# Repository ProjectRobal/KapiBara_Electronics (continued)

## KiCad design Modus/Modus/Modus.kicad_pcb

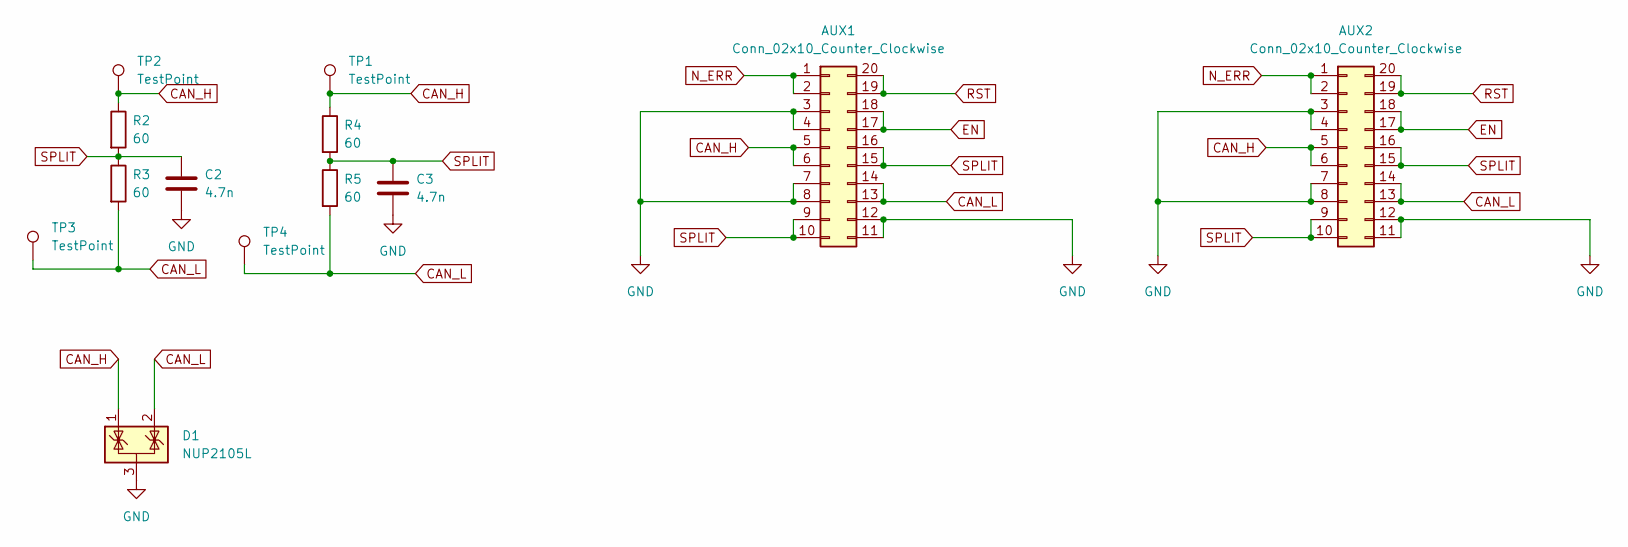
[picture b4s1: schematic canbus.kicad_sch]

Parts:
AUX1, AUX2: Conn_02x10_Counter_Clockwise; IDC-Header_2x10_P2.54mm_Vertical
C2, C3: 4.7n; C_0805_2012Metric_Pad1.18x1.45mm_HandSolder
D1: NUP2105L; SOT-23
R2, R3, R4, R5: 60; R_0805_2012Metric_Pad1.20x1.40mm_HandSolder
TP1, TP2, TP3, TP4: TestPoint; TestPoint_Pad_D2.0mm

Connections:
CAN_H: AUX1.5, AUX1.6, AUX2.5, AUX2.6, D1.1 (K), R2.1, R4.1, TP1.1, TP2.1; also elsewhere on the board
CAN_L: AUX1.13, AUX1.14, AUX2.13, AUX2.14, D1.2 (K), R3.2, R5.2, TP3.1, TP4.1; also elsewhere on the board
EN: AUX1.17, AUX1.18, AUX2.17, AUX2.18; also elsewhere on the board
GND: AUX1.3, AUX1.4, AUX1.7, AUX1.8, AUX1.11, AUX1.12, AUX2.3, AUX2.4, AUX2.7, AUX2.8, AUX2.11, AUX2.12, C2.2, C3.2, D1.3 (A); also elsewhere on the board
N_ERR: AUX1.1, AUX1.2, AUX2.1, AUX2.2; also elsewhere on the board
RST: AUX1.19, AUX1.20, AUX2.19, AUX2.20; also elsewhere on the board
SPLIT: AUX1.9, AUX1.10, AUX1.15, AUX1.16, AUX2.9, AUX2.10, AUX2.15, AUX2.16, C2.1, C3.1, R2.2, R3.1, R4.2, R5.1; also elsewhere on the board

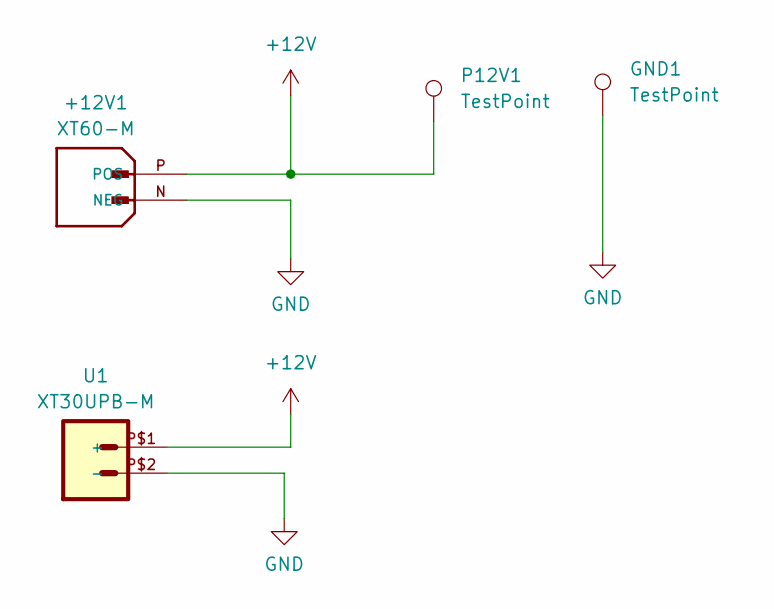
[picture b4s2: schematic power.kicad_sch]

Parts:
+12V1: XT60-M; AMASS_XT60-M; PARTREV V1.2
GND1: TestPoint; TestPoint_Pad_3.0x3.0mm
P12V1: TestPoint; TestPoint_Pad_3.0x3.0mm
U1: XT30UPB-M

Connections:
+12V: +12V1.P (POS), P12V1.1, U1.P$1 (+); also elsewhere on the board
GND: +12V1.N (NEG), GND1.1, U1.P$2 (-); also elsewhere on the board

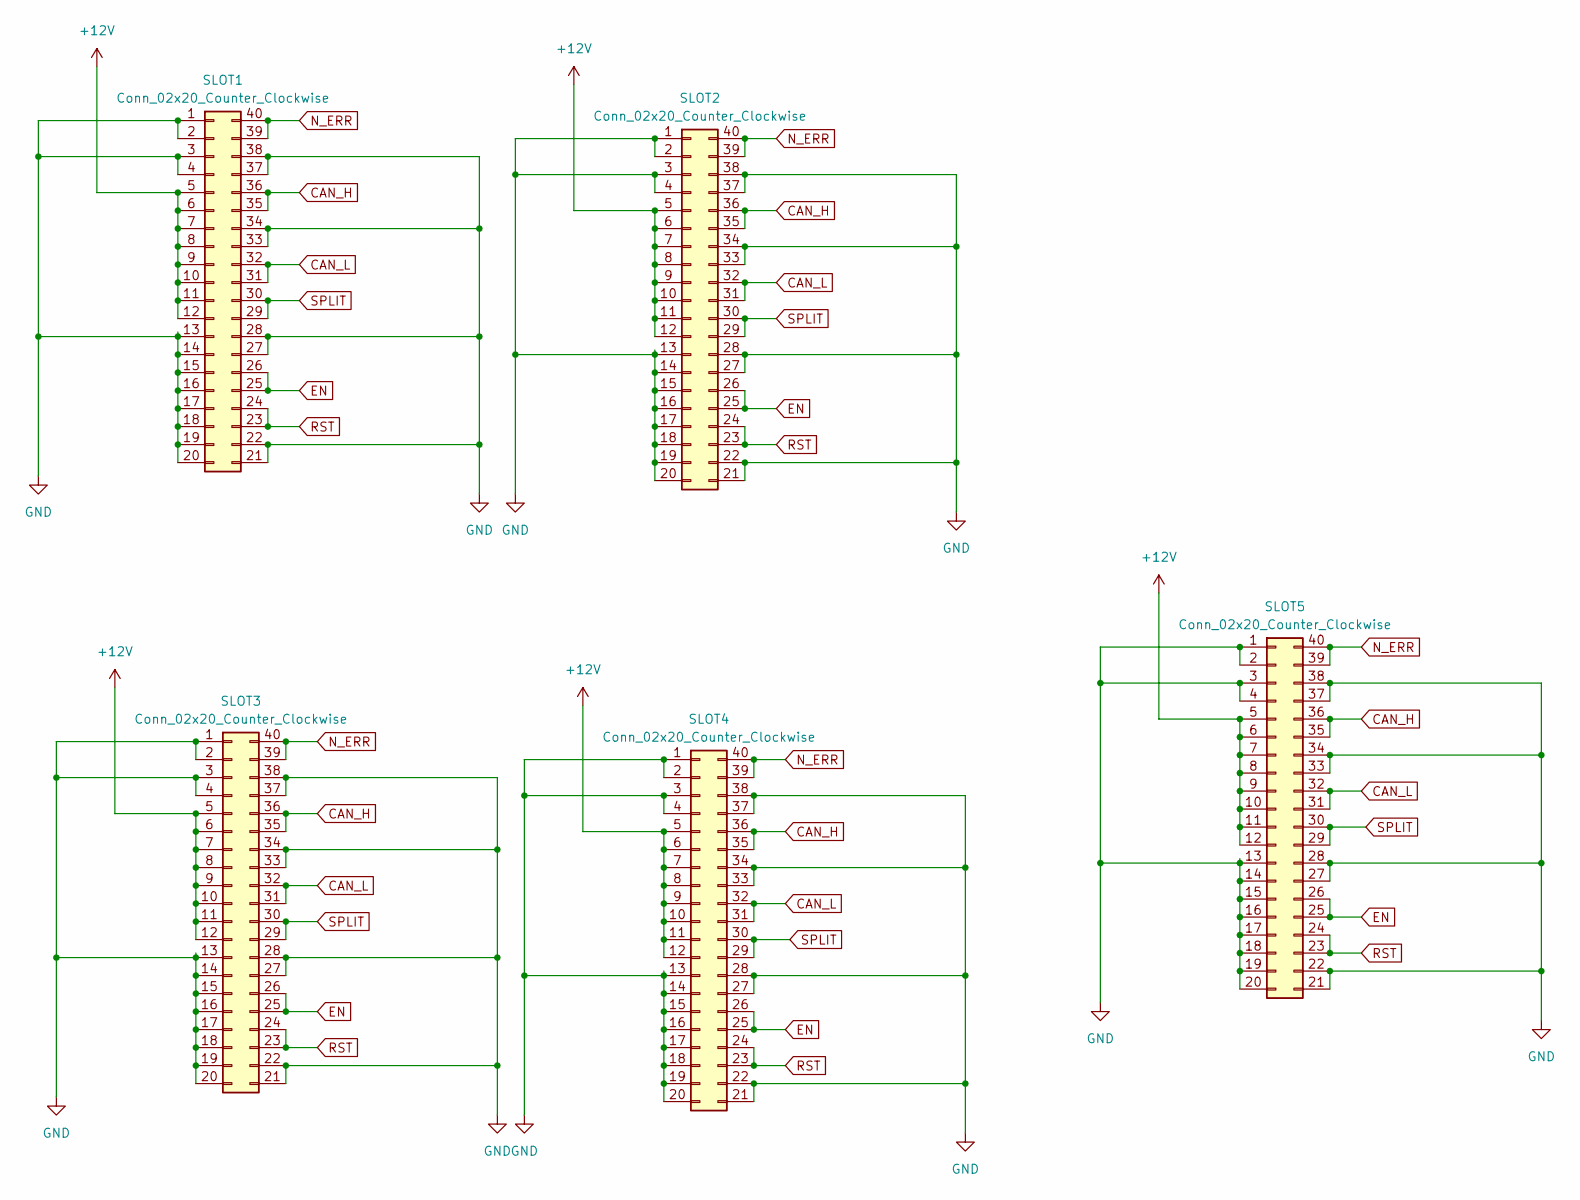
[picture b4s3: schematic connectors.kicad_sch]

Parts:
SLOT1, SLOT2, SLOT3, SLOT4, SLOT5: Conn_02x20_Counter_Clockwise; IDC-Header_2x20_P2.54mm_Vertical

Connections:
+12V: SLOT1.5, SLOT1.6, SLOT1.7, SLOT1.8, SLOT1.9, SLOT1.10, SLOT1.11, SLOT1.12, SLOT2.5, SLOT2.6, SLOT2.7, SLOT2.8, SLOT2.9, SLOT2.10, SLOT2.11, SLOT2.12, SLOT3.5, SLOT3.6, SLOT3.7, SLOT3.8, SLOT3.9, SLOT3.10, SLOT3.11, SLOT3.12, SLOT4.5, SLOT4.6, SLOT4.7, SLOT4.8, SLOT4.9, SLOT4.10, SLOT4.11, SLOT4.12, SLOT5.5, SLOT5.6, SLOT5.7, SLOT5.8, SLOT5.9, SLOT5.10, SLOT5.11, SLOT5.12; also elsewhere on the board
CAN_H: SLOT1.35, SLOT1.36, SLOT2.35, SLOT2.36, SLOT3.35, SLOT3.36, SLOT4.35, SLOT4.36, SLOT5.35, SLOT5.36; also elsewhere on the board
CAN_L: SLOT1.31, SLOT1.32, SLOT2.31, SLOT2.32, SLOT3.31, SLOT3.32, SLOT4.31, SLOT4.32, SLOT5.31, SLOT5.32; also elsewhere on the board
EN: SLOT1.25, SLOT1.26, SLOT2.25, SLOT2.26, SLOT3.25, SLOT3.26, SLOT4.25, SLOT4.26, SLOT5.25, SLOT5.26; also elsewhere on the board
GND: SLOT1.1, SLOT1.2, SLOT1.3, SLOT1.4, SLOT1.13, SLOT1.14, SLOT1.15, SLOT1.16, SLOT1.17, SLOT1.18, SLOT1.19, SLOT1.20, SLOT1.21, SLOT1.22, SLOT1.27, SLOT1.28, SLOT1.33, SLOT1.34, SLOT1.37, SLOT1.38, SLOT2.1, SLOT2.2, SLOT2.3, SLOT2.4, SLOT2.13, SLOT2.14, SLOT2.15, SLOT2.16, SLOT2.17, SLOT2.18, SLOT2.19, SLOT2.20, SLOT2.21, SLOT2.22, SLOT2.27, SLOT2.28, SLOT2.33, SLOT2.34, SLOT2.37, SLOT2.38, SLOT3.1, SLOT3.2, SLOT3.3, SLOT3.4, SLOT3.13, SLOT3.14, SLOT3.15, SLOT3.16, SLOT3.17, SLOT3.18, SLOT3.19, SLOT3.20, SLOT3.21, SLOT3.22, SLOT3.27, SLOT3.28, SLOT3.33, SLOT3.34, SLOT3.37, SLOT3.38, SLOT4.1, SLOT4.2, SLOT4.3, SLOT4.4, SLOT4.13, SLOT4.14, SLOT4.15, SLOT4.16, SLOT4.17, SLOT4.18, SLOT4.19, SLOT4.20, SLOT4.21, SLOT4.22, SLOT4.27, SLOT4.28, SLOT4.33, SLOT4.34, SLOT4.37, SLOT4.38, SLOT5.1, SLOT5.2, SLOT5.3, SLOT5.4, SLOT5.13, SLOT5.14, SLOT5.15, SLOT5.16, SLOT5.17, SLOT5.18, SLOT5.19, SLOT5.20, SLOT5.21, SLOT5.22, SLOT5.27, SLOT5.28, SLOT5.33, SLOT5.34, SLOT5.37, SLOT5.38; also elsewhere on the board
N_ERR: SLOT1.39, SLOT1.40, SLOT2.39, SLOT2.40, SLOT3.39, SLOT3.40, SLOT4.39, SLOT4.40, SLOT5.39, SLOT5.40; also elsewhere on the board
RST: SLOT1.23, SLOT1.24, SLOT2.23, SLOT2.24, SLOT3.23, SLOT3.24, SLOT4.23, SLOT4.24, SLOT5.23, SLOT5.24; also elsewhere on the board
SPLIT: SLOT1.29, SLOT1.30, SLOT2.29, SLOT2.30, SLOT3.29, SLOT3.30, SLOT4.29, SLOT4.30, SLOT5.29, SLOT5.30; also elsewhere on the board

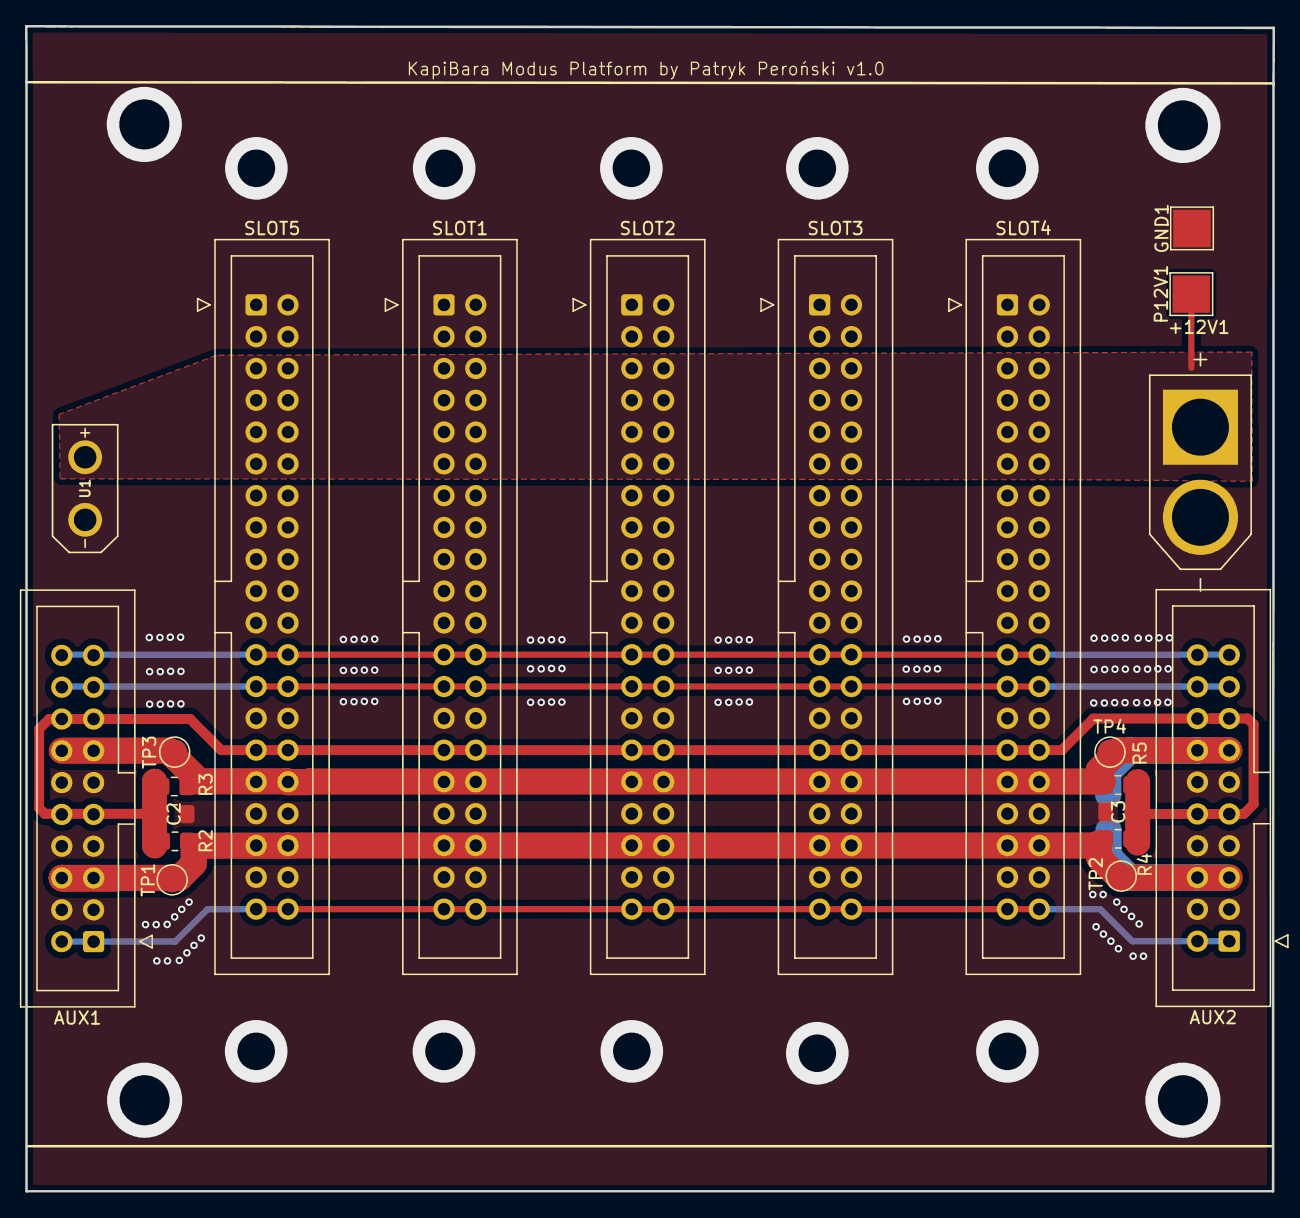
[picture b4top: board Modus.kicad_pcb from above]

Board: 2 copper layers, 99.6 x 93.0 mm, 22 parts (1 on the bottom side), 8 nets.

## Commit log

2025-04-07 Frist commit
2025-04-07 Added README
